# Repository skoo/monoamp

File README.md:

monoamp
=======

Small (34x29mm) 10-W Mono Class-D Audio Power Amplifier based on TPA3111D1.

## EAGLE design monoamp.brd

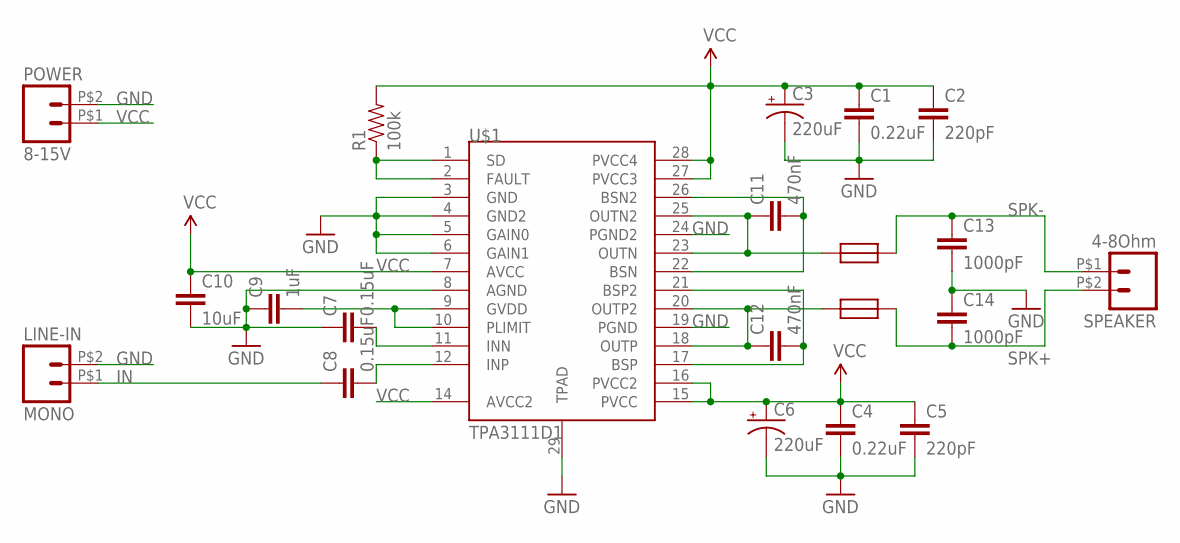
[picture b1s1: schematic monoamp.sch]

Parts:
C1, C4: 0.22uF; 0603-CAP
C2, C5: 220pF; 0603-CAP
C3, C6: 220uF; NICHICON_10
C7, C8: 0.15uF; 0603-CAP
C9: 1uF; 0603-CAP
C10: 10uF; 0805
C11, C12: 470nF; 0603-CAP
C13, C14: 1000pF; 0603-CAP
LINE-IN: MONO; 1X02_BIG
POWER: 8-15V; 1X02_BIG
R1: 100k; 0603-RES
SPEAKER: 4-8Ohm; 1X02_BIG
U$1: TPA3111D1; TSSOP28-GROUNDPAD
U$2, U$3: FERRITE-BEAD28L0138-80R-10; 0138

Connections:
GND: C1.2, C2.2, C3.-, C4.2, C5.2, C6.-, C7.1, C9.1, C10.2, C13.2, C14.1, LINE-IN.P$2 (2), POWER.P$2 (2), U$1.3 (GND), U$1.4 (GND2), U$1.5 (GAIN0), U$1.6 (GAIN1), U$1.8 (AGND), U$1.19 (PGND), U$1.24 (PGND2), U$1.29 (TPAD)
IN: C8.1, LINE-IN.P$1 (1)
unnamed: C7.2, U$1.11 (INN)
unnamed: C8.2, U$1.12 (INP)
unnamed: C9.2, U$1.9 (GVDD), U$1.10 (PLIMIT)
unnamed: R1.1, U$1.1 (SD), U$1.2 (FAULT)
unnamed: C11.2, U$1.22 (BSN), U$1.26 (BSN2)
unnamed: C12.2, U$1.17 (BSP), U$1.21 (BSP2)
unnamed: C11.1, U$1.23 (OUTN), U$1.25 (OUTN2), U$2.P$1
unnamed: C12.1, U$1.18 (OUTP), U$1.20 (OUTP2), U$3.P$1
SPK+: C14.2, SPEAKER.P$2 (2), U$3.P$2
SPK-: C13.1, SPEAKER.P$1 (1), U$2.P$2
VCC: C1.1, C2.1, C3.+, C4.1, C5.1, C6.+, C10.1, POWER.P$1 (1), R1.2, U$1.7 (AVCC), U$1.14 (AVCC2), U$1.15 (PVCC), U$1.16 (PVCC2), U$1.27 (PVCC3), U$1.28 (PVCC4)

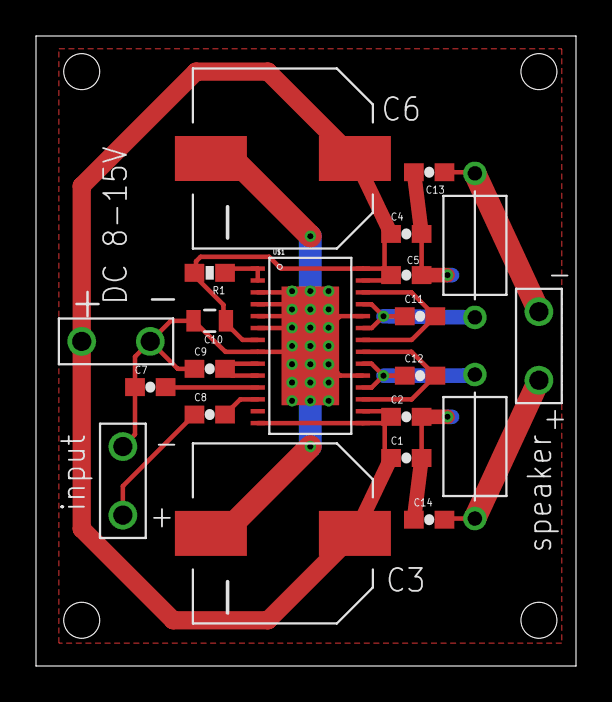
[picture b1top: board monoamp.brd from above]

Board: 2 copper layers, 30.0 x 35.0 mm, 21 parts (0 on the bottom side), 13 nets.

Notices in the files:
parts and their libraries:
SparkFun: Licensing: CC v3.0 Share-Alike You are welcome to use this library for commercial purposes.
